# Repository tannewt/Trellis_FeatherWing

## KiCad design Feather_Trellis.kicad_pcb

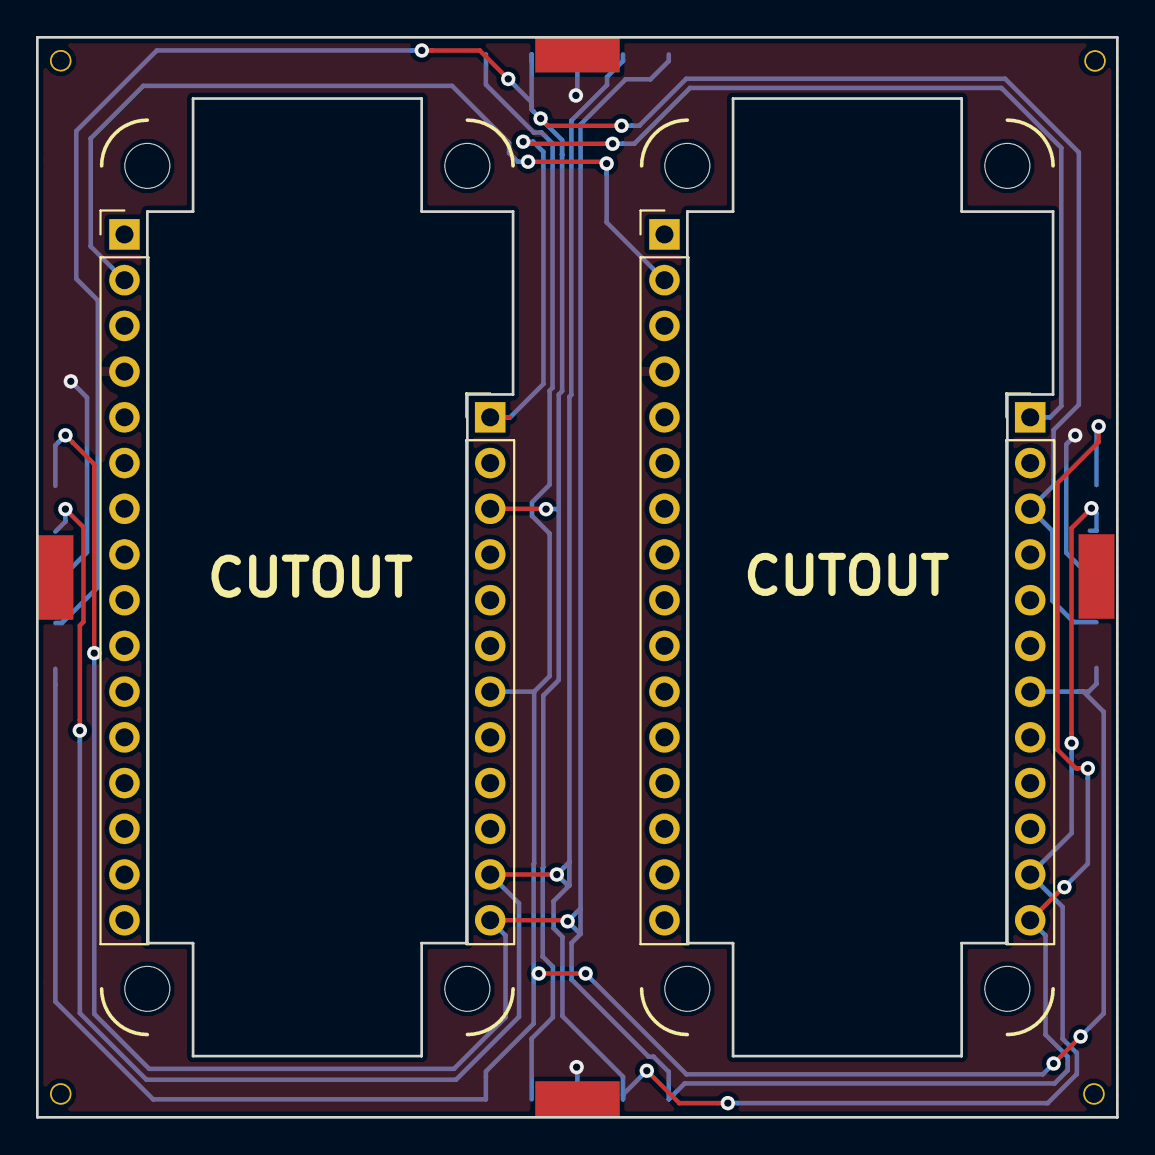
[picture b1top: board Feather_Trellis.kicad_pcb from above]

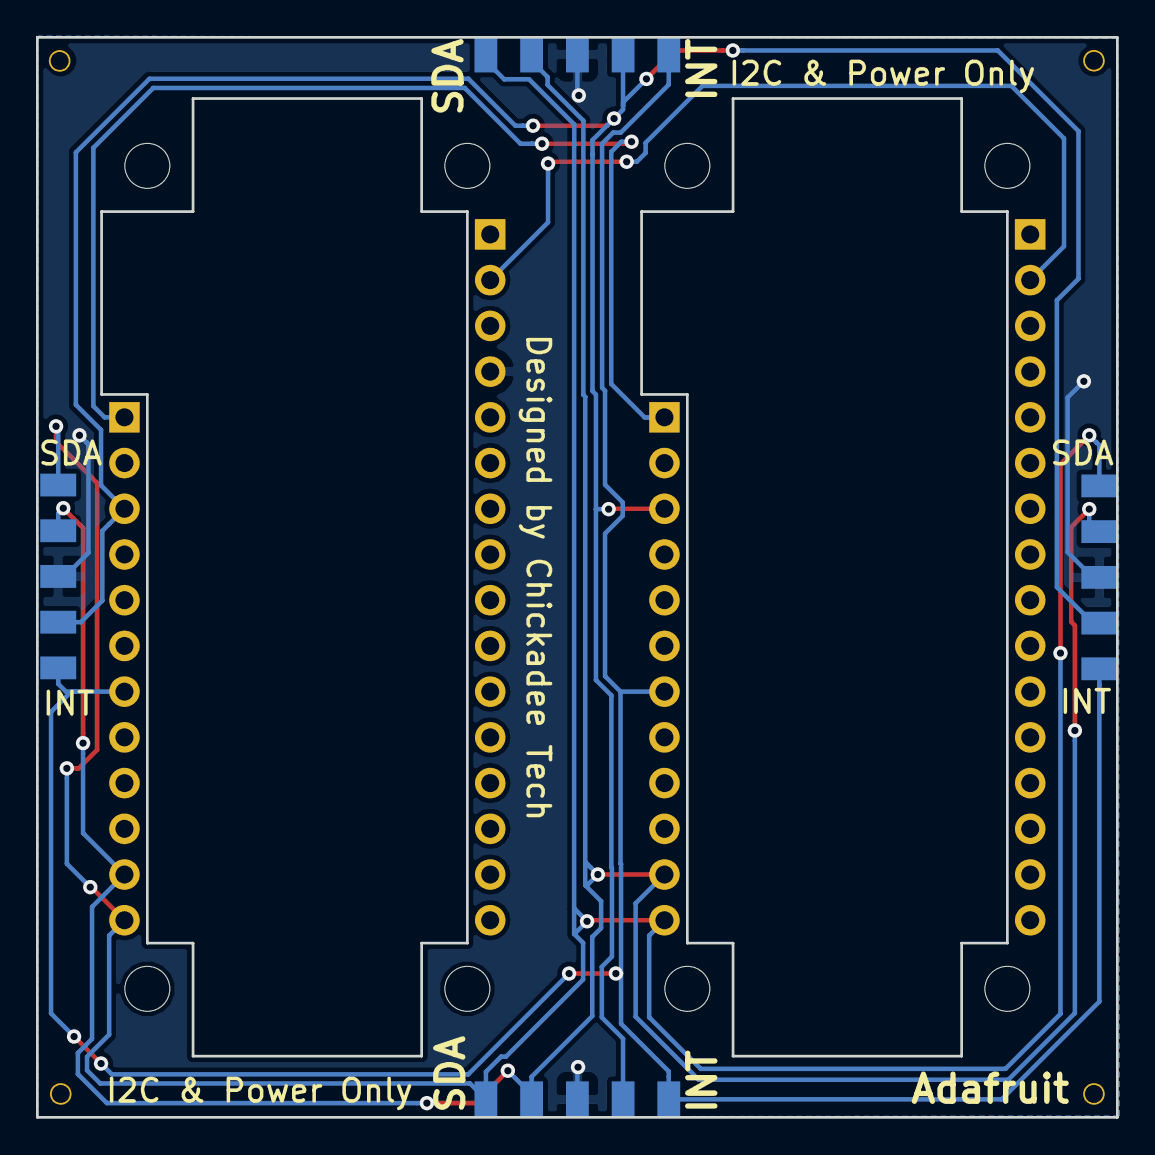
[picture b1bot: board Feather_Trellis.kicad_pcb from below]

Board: 2 copper layers, 60.0 x 60.0 mm, 20 parts (4 on the bottom side), 7 nets.

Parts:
J1, J3: FeatherTop; Pin_Header_Straight_1x12_Pitch2.54mm
J2, J4: FeatherBottom; Pin_Header_Straight_1x16_Pitch2.54mm
J5, J7: Conn_01x05; Trellis Interconnect
J6, J8: Conn_01x05; Trellis_Interconnect_Bottom_Right
J9, J10, J11, J12, J13, J14, J15, J16: Conn_01x01; MountingHole_2.5mm
J17, J18, J19, J20: Conn_01x01; 1mm_mount

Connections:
+3V3: J2.2, J4.2
+5V: J1.3, J3.3, J5.4, J6.4, J7.4, J8.4
/BAT: J1.1, J3.1
/INT: J1.7, J3.7, J5.5, J6.5, J7.5, J8.5
/SCL: J1.11, J3.11, J5.2, J6.2, J7.2, J8.2
/SDA: J1.12, J3.12, J5.1, J6.1, J7.1, J8.1
GND: J2.4, J4.4, J5.3, J6.3, J7.3, J8.3

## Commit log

2018-03-20 Initial design. Rev A from OSH Park.
